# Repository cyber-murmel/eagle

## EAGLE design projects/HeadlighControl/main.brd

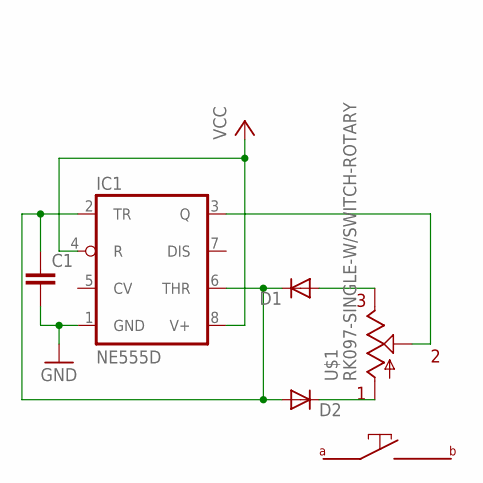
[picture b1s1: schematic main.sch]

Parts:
C1: C-EUC0603; C0603
D1, D2: DIODE-MICROMELF-W; MICROMELF-W
IC1: NE555D; SO08
U$1: RK097-SINGLE-W/SWITCH-ROTARY; RK097-DUAL-ELEMENT-W/SWITCH

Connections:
GND: C1.2, IC1.1 (GND)
unnamed: IC1.3 (Q), U$1.P$5 (S), U$1.P$6 (S1)
unnamed: D2.C, U$1.P$1 (A), U$1.P$2 (A1)
unnamed: D1.A, U$1.P$3 (E), U$1.P$4 (E1)
unnamed: C1.1, D1.C, D2.A, IC1.2 (TR), IC1.6 (THR)
VCC: IC1.4 (R), IC1.8 (V+)

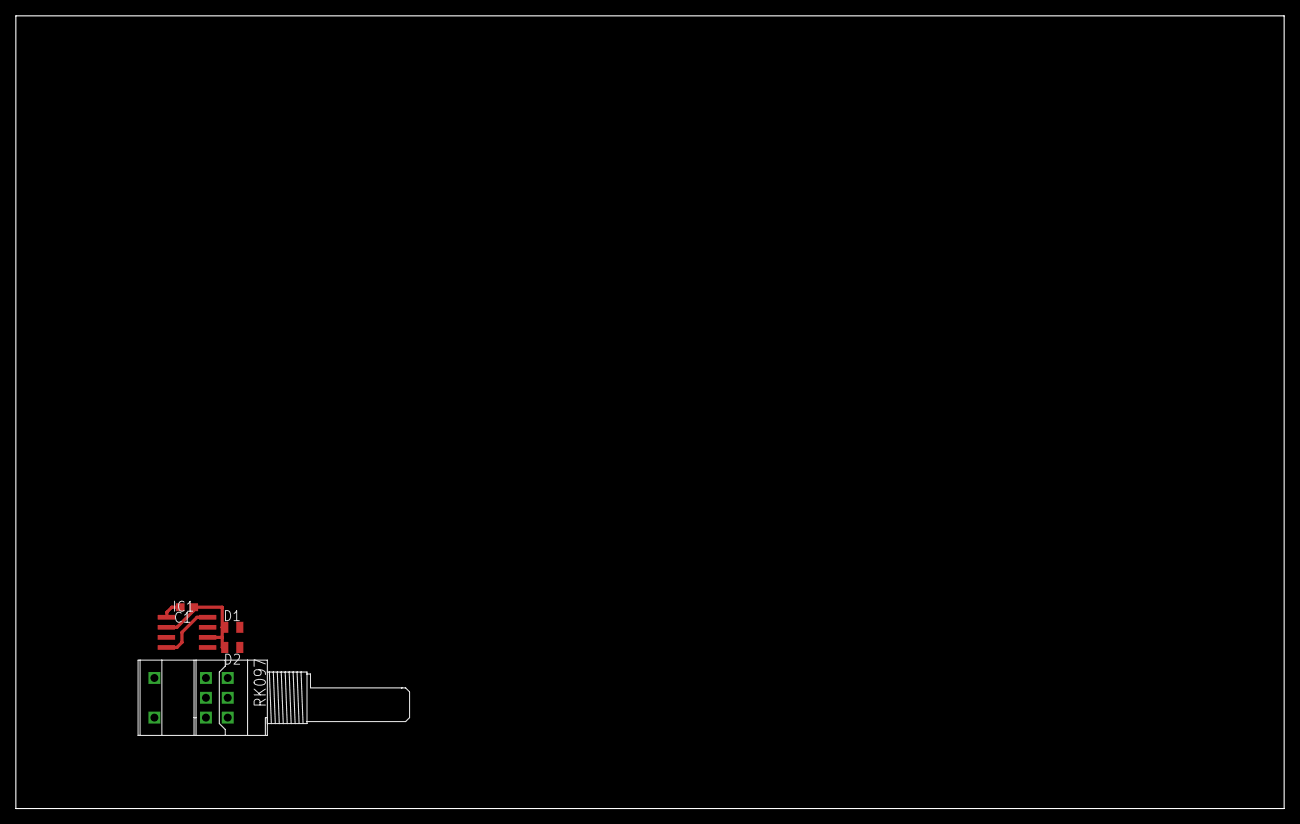
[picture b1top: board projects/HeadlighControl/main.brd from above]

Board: 2 copper layers, 160.0 x 100.0 mm, 5 parts (0 on the bottom side), 6 nets.

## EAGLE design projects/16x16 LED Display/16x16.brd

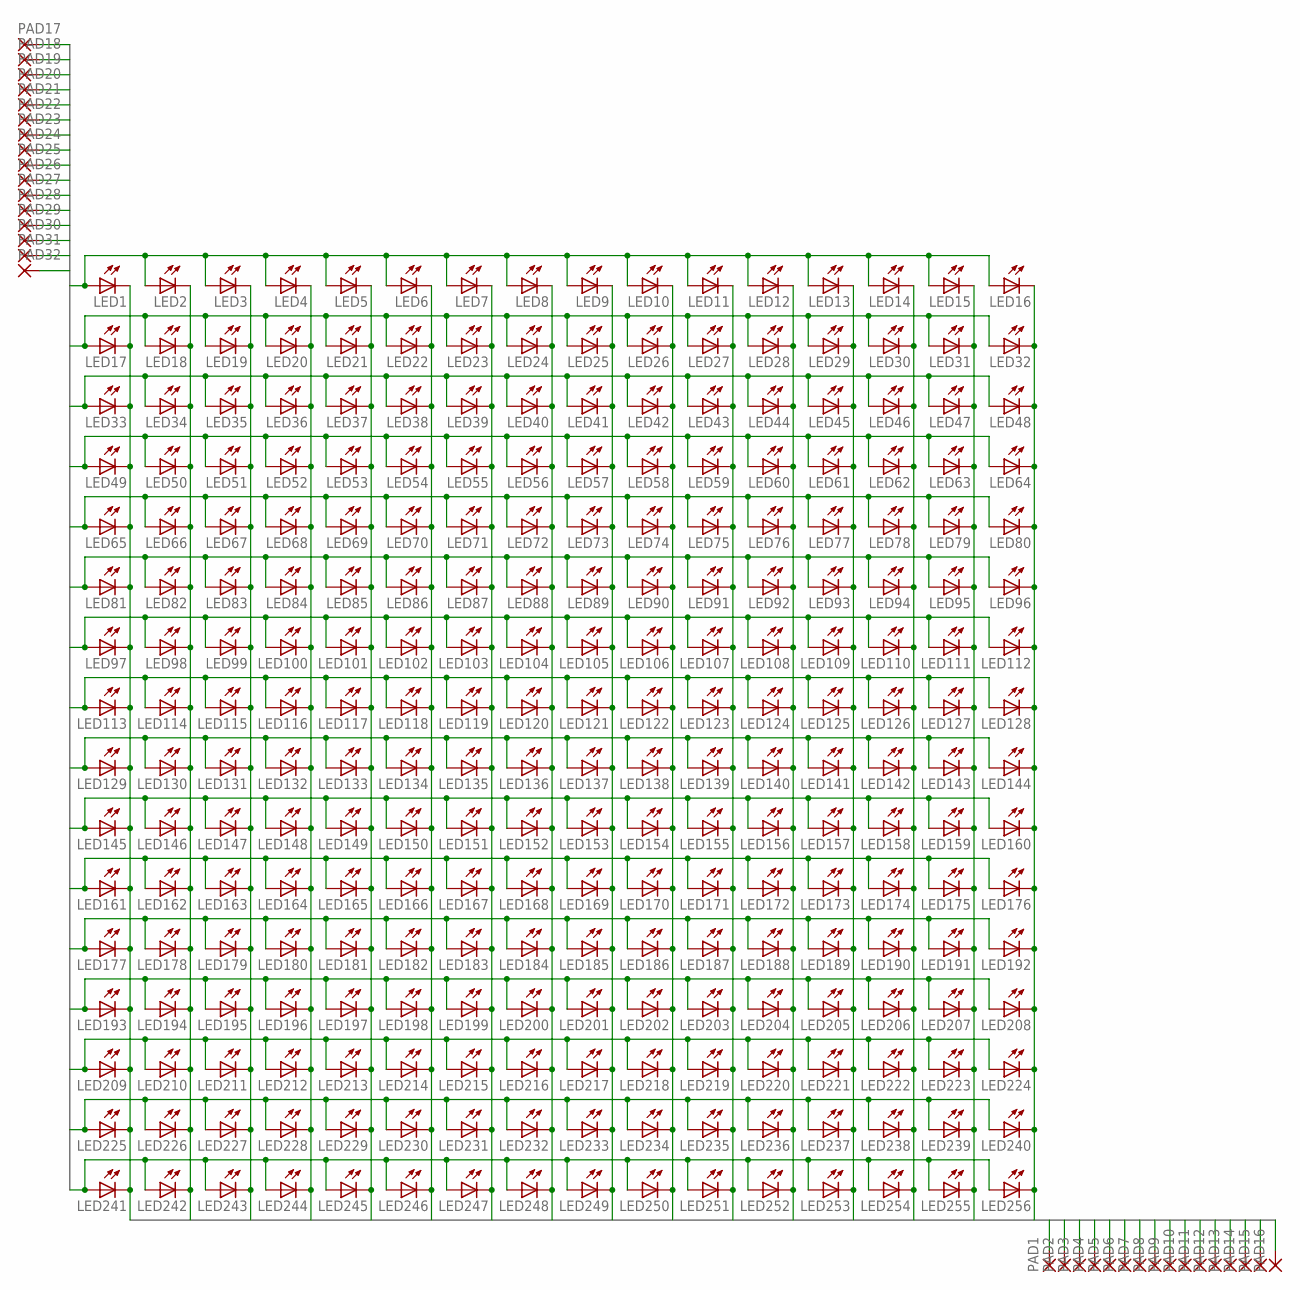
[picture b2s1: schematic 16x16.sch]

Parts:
LED1, LED2, LED3, LED4, LED5, LED6, LED7, LED8, LED9, LED10, LED11, LED12, LED13, LED14, LED15, LED16, LED17, LED18, LED19, LED20, LED21, LED22, LED23, LED24, LED25, LED26, LED27, LED28, LED29, LED30, LED31, LED32, LED33, LED34, LED35, LED36, LED37, LED38, LED39, LED40, LED41, LED42, LED43, LED44, LED45, LED46, LED47, LED48, LED49, LED50, LED51, LED52, LED53, LED54, LED55, LED56, LED57, LED58, LED59, LED60, LED61, LED62, LED63, LED64, LED65, LED66, LED67, LED68, LED69, LED70, LED71, LED72, LED73, LED74, LED75, LED76, LED77, LED78, LED79, LED80, LED81, LED82, LED83, LED84, LED85, LED86, LED87, LED88, LED89, LED90, LED91, LED92, LED93, LED94, LED95, LED96, LED97, LED98, LED99, LED100, LED101, LED102, LED103, LED104, LED105, LED106, LED107, LED108, LED109, LED110, LED111, LED112, LED113, LED114, LED115, LED116, LED117, LED118, LED119, LED120, LED121, LED122, LED123, LED124, LED125, LED126, LED127, LED128, LED129, LED130, LED131, LED132, LED133, LED134, LED135, LED136, LED137, LED138, LED139, LED140, LED141, LED142, LED143, LED144, LED145, LED146, LED147, LED148, LED149, LED150, LED151, LED152, LED153, LED154, LED155, LED156, LED157, LED158, LED159, LED160, LED161, LED162, LED163, LED164, LED165, LED166, LED167, LED168, LED169, LED170, LED171, LED172, LED173, LED174, LED175, LED176, LED177, LED178, LED179, LED180, LED181, LED182, LED183, LED184, LED185, LED186, LED187, LED188, LED189, LED190, LED191, LED192, LED193, LED194, LED195, LED196, LED197, LED198, LED199, LED200, LED201, LED202, LED203, LED204, LED205, LED206, LED207, LED208, LED209, LED210, LED211, LED212, LED213, LED214, LED215, LED216, LED217, LED218, LED219, LED220, LED221, LED222, LED223, LED224, LED225, LED226, LED227, LED228, LED229, LED230, LED231, LED232, LED233, LED234, LED235, LED236, LED237, LED238, LED239, LED240, LED241, LED242, LED243, LED244, LED245, LED246, LED247, LED248, LED249, LED250, LED251, LED252, LED253, LED254, LED255, LED256: LEDSML0603; SML0603
PAD1, PAD2, PAD3, PAD4, PAD5, PAD6, PAD7, PAD8, PAD9, PAD10, PAD11, PAD12, PAD13, PAD14, PAD15, PAD16, PAD17, PAD18, PAD19, PAD20, PAD21, PAD22, PAD23, PAD24, PAD25, PAD26, PAD27, PAD28, PAD29, PAD30, PAD31, PAD32: SMD2; SMD1,27-2,54

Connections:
X0: LED1.C, LED17.C, LED33.C, LED49.C, LED65.C, LED81.C, LED97.C, LED113.C, LED129.C, LED145.C, LED161.C, LED177.C, LED193.C, LED209.C, LED225.C, LED241.C, PAD1.1
X1: LED2.C, LED18.C, LED34.C, LED50.C, LED66.C, LED82.C, LED98.C, LED114.C, LED130.C, LED146.C, LED162.C, LED178.C, LED194.C, LED210.C, LED226.C, LED242.C, PAD2.1
X2: LED3.C, LED19.C, LED35.C, LED51.C, LED67.C, LED83.C, LED99.C, LED115.C, LED131.C, LED147.C, LED163.C, LED179.C, LED195.C, LED211.C, LED227.C, LED243.C, PAD3.1
X3: LED4.C, LED20.C, LED36.C, LED52.C, LED68.C, LED84.C, LED100.C, LED116.C, LED132.C, LED148.C, LED164.C, LED180.C, LED196.C, LED212.C, LED228.C, LED244.C, PAD4.1
X4: LED5.C, LED21.C, LED37.C, LED53.C, LED69.C, LED85.C, LED101.C, LED117.C, LED133.C, LED149.C, LED165.C, LED181.C, LED197.C, LED213.C, LED229.C, LED245.C, PAD5.1
X5: LED6.C, LED22.C, LED38.C, LED54.C, LED70.C, LED86.C, LED102.C, LED118.C, LED134.C, LED150.C, LED166.C, LED182.C, LED198.C, LED214.C, LED230.C, LED246.C, PAD6.1
X6: LED7.C, LED23.C, LED39.C, LED55.C, LED71.C, LED87.C, LED103.C, LED119.C, LED135.C, LED151.C, LED167.C, LED183.C, LED199.C, LED215.C, LED231.C, LED247.C, PAD7.1
X7: LED8.C, LED24.C, LED40.C, LED56.C, LED72.C, LED88.C, LED104.C, LED120.C, LED136.C, LED152.C, LED168.C, LED184.C, LED200.C, LED216.C, LED232.C, LED248.C, PAD8.1
X8: LED9.C, LED25.C, LED41.C, LED57.C, LED73.C, LED89.C, LED105.C, LED121.C, LED137.C, LED153.C, LED169.C, LED185.C, LED201.C, LED217.C, LED233.C, LED249.C, PAD9.1
X9: LED10.C, LED26.C, LED42.C, LED58.C, LED74.C, LED90.C, LED106.C, LED122.C, LED138.C, LED154.C, LED170.C, LED186.C, LED202.C, LED218.C, LED234.C, LED250.C, PAD10.1
X10: LED11.C, LED27.C, LED43.C, LED59.C, LED75.C, LED91.C, LED107.C, LED123.C, LED139.C, LED155.C, LED171.C, LED187.C, LED203.C, LED219.C, LED235.C, LED251.C, PAD11.1
X11: LED12.C, LED28.C, LED44.C, LED60.C, LED76.C, LED92.C, LED108.C, LED124.C, LED140.C, LED156.C, LED172.C, LED188.C, LED204.C, LED220.C, LED236.C, LED252.C, PAD12.1
X12: LED13.C, LED29.C, LED45.C, LED61.C, LED77.C, LED93.C, LED109.C, LED125.C, LED141.C, LED157.C, LED173.C, LED189.C, LED205.C, LED221.C, LED237.C, LED253.C, PAD13.1
X13: LED14.C, LED30.C, LED46.C, LED62.C, LED78.C, LED94.C, LED110.C, LED126.C, LED142.C, LED158.C, LED174.C, LED190.C, LED206.C, LED222.C, LED238.C, LED254.C, PAD14.1
X14: LED15.C, LED31.C, LED47.C, LED63.C, LED79.C, LED95.C, LED111.C, LED127.C, LED143.C, LED159.C, LED175.C, LED191.C, LED207.C, LED223.C, LED239.C, LED255.C, PAD15.1
X15: LED16.C, LED32.C, LED48.C, LED64.C, LED80.C, LED96.C, LED112.C, LED128.C, LED144.C, LED160.C, LED176.C, LED192.C, LED208.C, LED224.C, LED240.C, LED256.C, PAD16.1
Y0: LED1.A, LED2.A, LED3.A, LED4.A, LED5.A, LED6.A, LED7.A, LED8.A, LED9.A, LED10.A, LED11.A, LED12.A, LED13.A, LED14.A, LED15.A, LED16.A, PAD17.1
Y1: LED17.A, LED18.A, LED19.A, LED20.A, LED21.A, LED22.A, LED23.A, LED24.A, LED25.A, LED26.A, LED27.A, LED28.A, LED29.A, LED30.A, LED31.A, LED32.A, PAD18.1
Y2: LED33.A, LED34.A, LED35.A, LED36.A, LED37.A, LED38.A, LED39.A, LED40.A, LED41.A, LED42.A, LED43.A, LED44.A, LED45.A, LED46.A, LED47.A, LED48.A, PAD19.1
Y3: LED49.A, LED50.A, LED51.A, LED52.A, LED53.A, LED54.A, LED55.A, LED56.A, LED57.A, LED58.A, LED59.A, LED60.A, LED61.A, LED62.A, LED63.A, LED64.A, PAD20.1
Y4: LED65.A, LED66.A, LED67.A, LED68.A, LED69.A, LED70.A, LED71.A, LED72.A, LED73.A, LED74.A, LED75.A, LED76.A, LED77.A, LED78.A, LED79.A, LED80.A, PAD21.1
Y5: LED81.A, LED82.A, LED83.A, LED84.A, LED85.A, LED86.A, LED87.A, LED88.A, LED89.A, LED90.A, LED91.A, LED92.A, LED93.A, LED94.A, LED95.A, LED96.A, PAD22.1
Y6: LED97.A, LED98.A, LED99.A, LED100.A, LED101.A, LED102.A, LED103.A, LED104.A, LED105.A, LED106.A, LED107.A, LED108.A, LED109.A, LED110.A, LED111.A, LED112.A, PAD23.1
Y7: LED113.A, LED114.A, LED115.A, LED116.A, LED117.A, LED118.A, LED119.A, LED120.A, LED121.A, LED122.A, LED123.A, LED124.A, LED125.A, LED126.A, LED127.A, LED128.A, PAD24.1
Y8: LED129.A, LED130.A, LED131.A, LED132.A, LED133.A, LED134.A, LED135.A, LED136.A, LED137.A, LED138.A, LED139.A, LED140.A, LED141.A, LED142.A, LED143.A, LED144.A, PAD25.1
Y9: LED145.A, LED146.A, LED147.A, LED148.A, LED149.A, LED150.A, LED151.A, LED152.A, LED153.A, LED154.A, LED155.A, LED156.A, LED157.A, LED158.A, LED159.A, LED160.A, PAD26.1
Y10: LED161.A, LED162.A, LED163.A, LED164.A, LED165.A, LED166.A, LED167.A, LED168.A, LED169.A, LED170.A, LED171.A, LED172.A, LED173.A, LED174.A, LED175.A, LED176.A, PAD27.1
Y11: LED177.A, LED178.A, LED179.A, LED180.A, LED181.A, LED182.A, LED183.A, LED184.A, LED185.A, LED186.A, LED187.A, LED188.A, LED189.A, LED190.A, LED191.A, LED192.A, PAD28.1
Y12: LED193.A, LED194.A, LED195.A, LED196.A, LED197.A, LED198.A, LED199.A, LED200.A, LED201.A, LED202.A, LED203.A, LED204.A, LED205.A, LED206.A, LED207.A, LED208.A, PAD29.1
Y13: LED209.A, LED210.A, LED211.A, LED212.A, LED213.A, LED214.A, LED215.A, LED216.A, LED217.A, LED218.A, LED219.A, LED220.A, LED221.A, LED222.A, LED223.A, LED224.A, PAD30.1
Y14: LED225.A, LED226.A, LED227.A, LED228.A, LED229.A, LED230.A, LED231.A, LED232.A, LED233.A, LED234.A, LED235.A, LED236.A, LED237.A, LED238.A, LED239.A, LED240.A, PAD31.1
Y15: LED241.A, LED242.A, LED243.A, LED244.A, LED245.A, LED246.A, LED247.A, LED248.A, LED249.A, LED250.A, LED251.A, LED252.A, LED253.A, LED254.A, LED255.A, LED256.A, PAD32.1

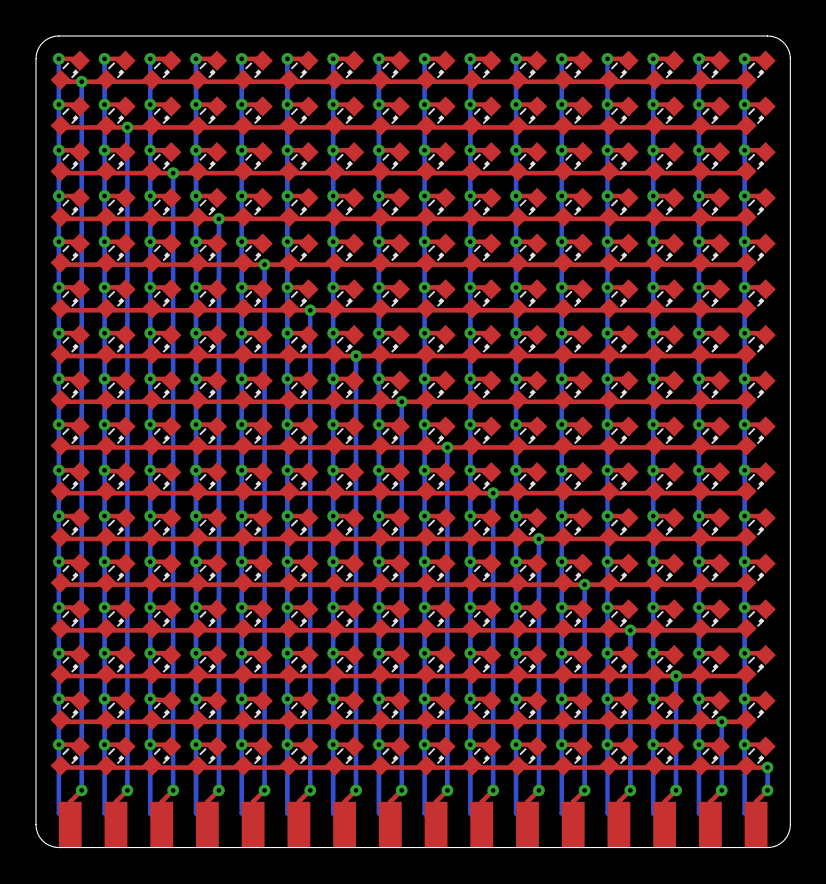
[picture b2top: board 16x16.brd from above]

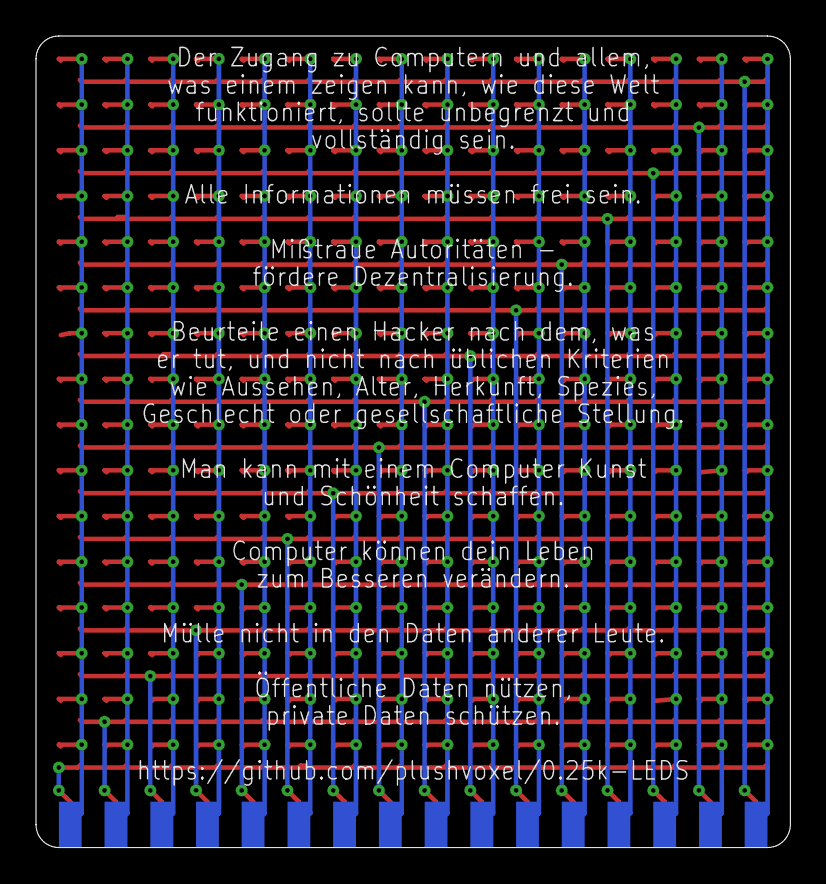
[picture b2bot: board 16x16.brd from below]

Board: 2 copper layers, 41.9 x 45.1 mm, 288 parts (16 on the bottom side), 32 nets.

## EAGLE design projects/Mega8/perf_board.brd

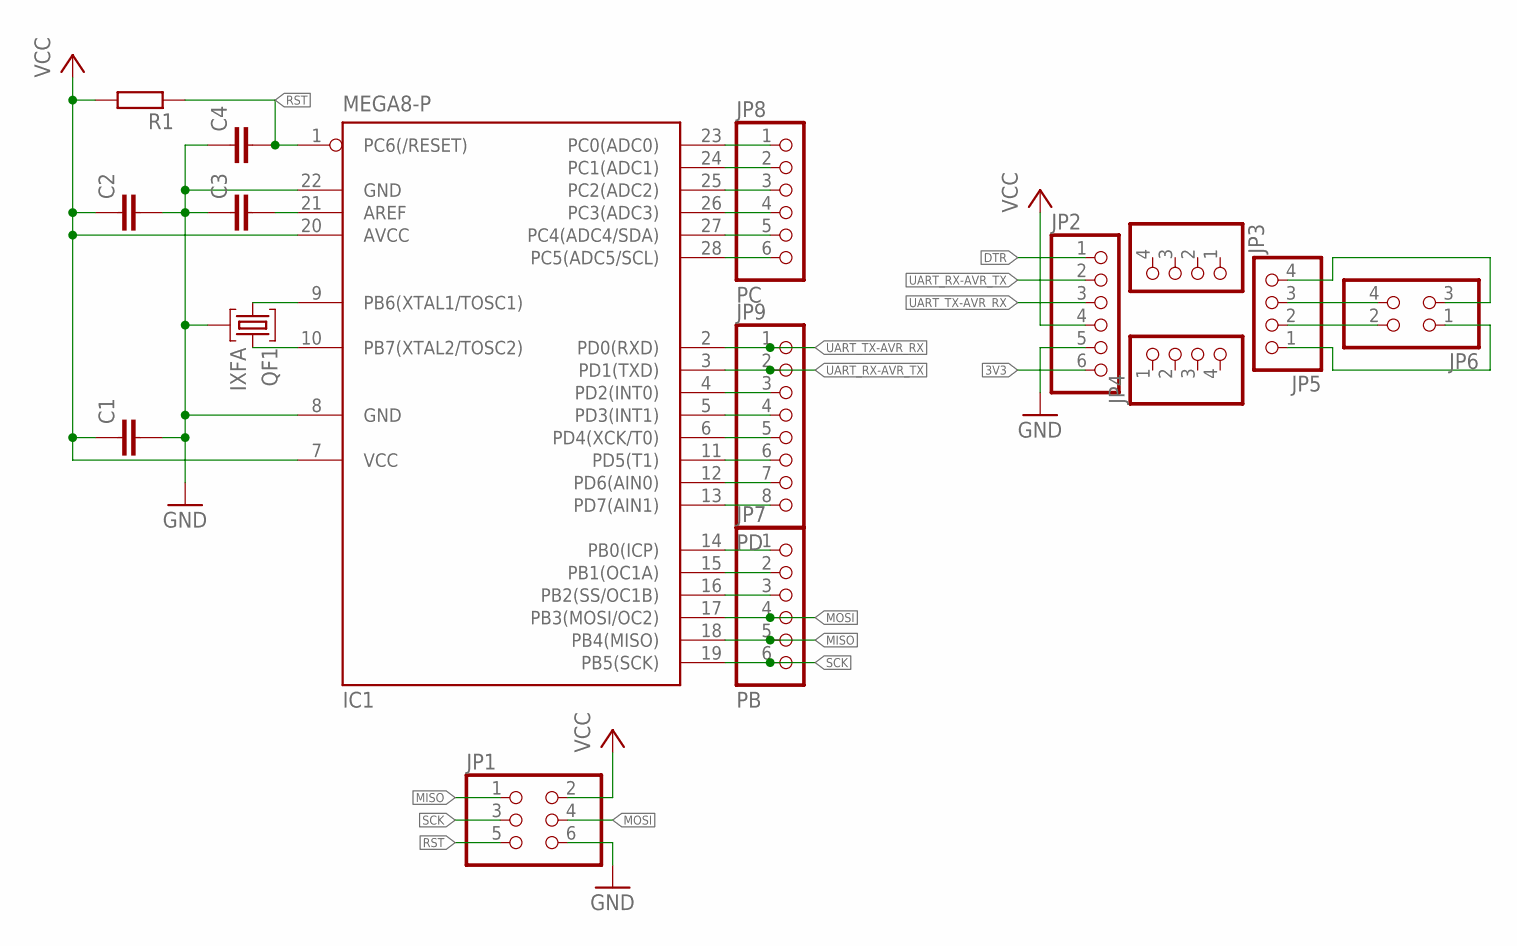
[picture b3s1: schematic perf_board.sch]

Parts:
C1, C2, C3, C4: C-EUC0603; C0603
IC1: MEGA8-P; DIL28-3
JP1: PINHD-2X3; 2X03
JP2: PINHD-1X6; 1X06
JP3, JP4, JP5: PINHD-1X4; 1X04
JP6: PINHD-2X2; 2X02
JP7: PB; 1X06
JP8: PC; 1X06
JP9: PD; 1X08
QF1: IXFA; HC49U
R1: R-EU_R0603; R0603

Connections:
3V3: JP2.6
DTR: JP2.1
GND: C1.2, C2.2, C3.1, C4.1, IC1.8 (GND), IC1.22 (GND), JP1.6, JP2.5, QF1.2
MISO: IC1.18 (PB4(MISO)), JP1.1, JP7.5
MOSI: IC1.17 (PB3(MOSI/OC2)), JP1.4, JP7.4
unnamed: C3.2, IC1.21 (AREF)
unnamed: IC1.9 (PB6(XTAL1/TOSC1)), QF1.1
unnamed: IC1.10 (PB7(XTAL2/TOSC2)), QF1.3
unnamed: JP5.2, JP6.2
unnamed: JP5.1, JP6.1
unnamed: JP5.3, JP6.4
unnamed: JP5.4, JP6.3
unnamed: IC1.14 (PB0(ICP)), JP7.1
unnamed: IC1.15 (PB1(OC1A)), JP7.2
unnamed: IC1.16 (PB2(SS/OC1B)), JP7.3
unnamed: IC1.4 (PD2(INT0)), JP9.3
unnamed: IC1.5 (PD3(INT1)), JP9.4
unnamed: IC1.6 (PD4(XCK/T0)), JP9.5
unnamed: IC1.11 (PD5(T1)), JP9.6
unnamed: IC1.12 (PD6(AIN0)), JP9.7
unnamed: IC1.13 (PD7(AIN1)), JP9.8
unnamed: IC1.23 (PC0(ADC0)), JP8.1
unnamed: IC1.24 (PC1(ADC1)), JP8.2
unnamed: IC1.25 (PC2(ADC2)), JP8.3
unnamed: IC1.26 (PC3(ADC3)), JP8.4
unnamed: IC1.27 (PC4(ADC4/SDA)), JP8.5
unnamed: IC1.28 (PC5(ADC5/SCL)), JP8.6
RST: C4.2, IC1.1 (PC6(/RESET)), JP1.5, R1.1
SCK: IC1.19 (PB5(SCK)), JP1.3, JP7.6
UART_RX-AVR_TX: IC1.3 (PD1(TXD)), JP2.2, JP9.2
UART_TX-AVR_RX: IC1.2 (PD0(RXD)), JP2.3, JP9.1
VCC: C1.1, C2.1, IC1.7 (VCC), IC1.20 (AVCC), JP1.2, JP2.4, R1.2

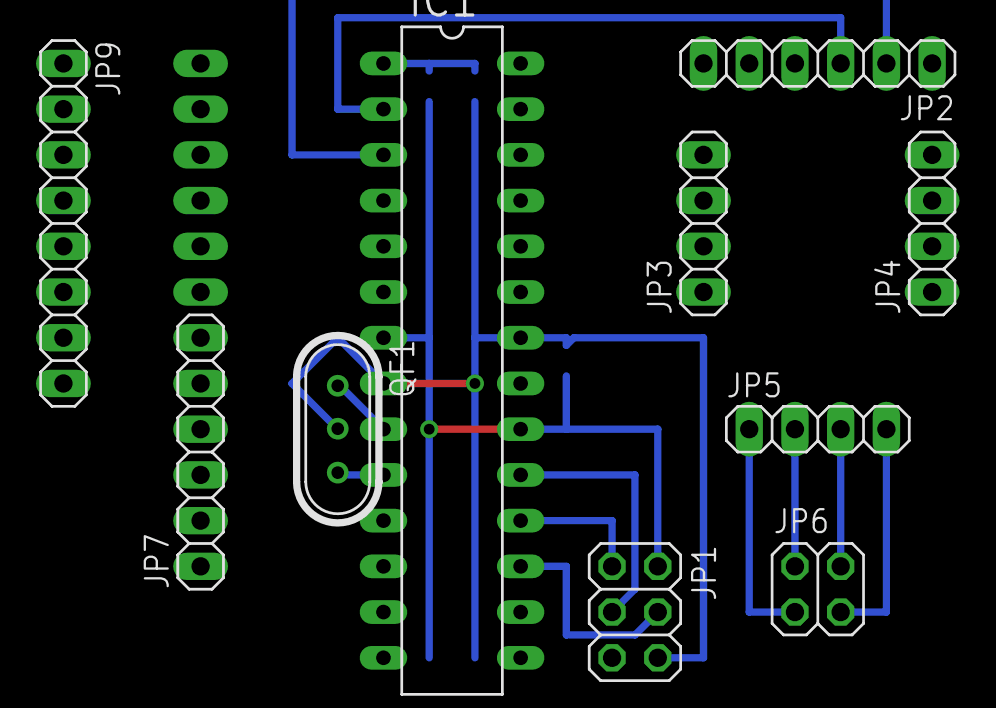
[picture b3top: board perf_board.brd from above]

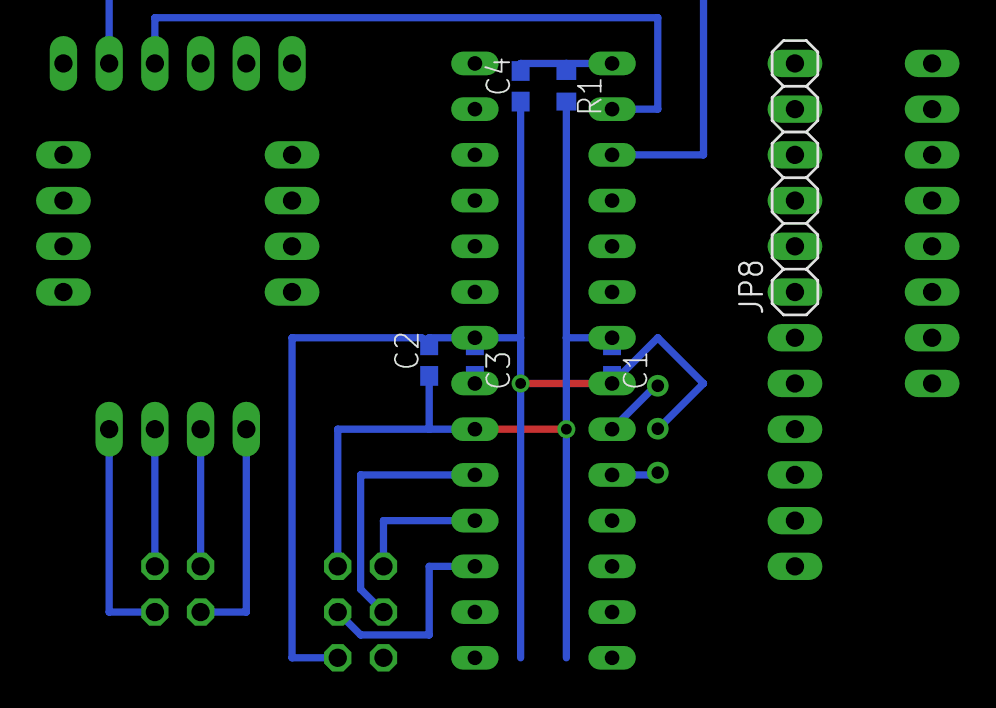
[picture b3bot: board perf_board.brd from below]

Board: 2 copper layers, 16 parts (6 on the bottom side), 30 nets.

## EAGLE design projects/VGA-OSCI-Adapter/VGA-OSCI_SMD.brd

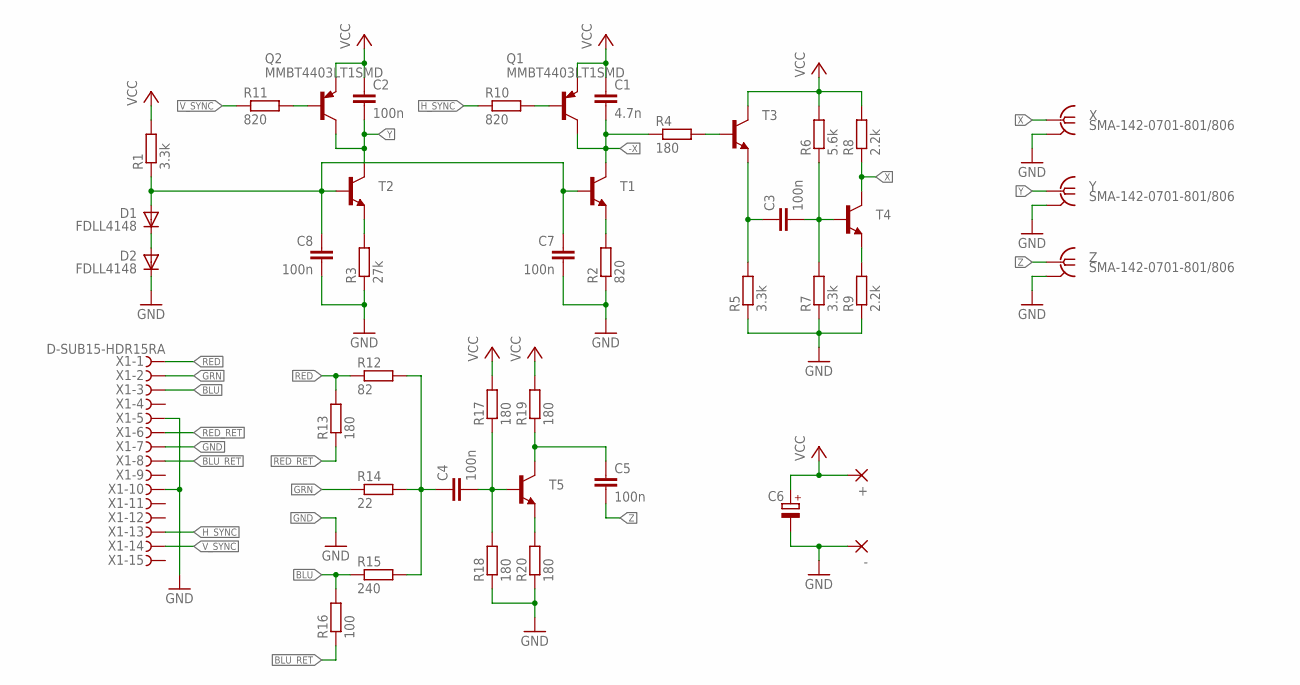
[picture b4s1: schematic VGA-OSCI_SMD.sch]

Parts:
+: WIREPADSMD1,27-254; SMD1,27-2,54
-: WIREPADSMD1,27-254; SMD1,27-2,54
C1: 4.7n; C0603
C2, C3, C4, C5, C7, C8: 100n; C0603
C6: CPOL-EU153CLV-0810; 153CLV-0810
D1, D2: FDLL4148; SOD80C
Q1, Q2: MMBT4403LT1SMD; SOT23-BEC
R1, R5, R7: 3.3k; R0603
R2, R10, R11: 820; R0603
R3: 27k; R0603
R4, R13, R17, R18, R19, R20: 180; R0603
R6: 5.6k; R0603
R8, R9: 2.2k; R0603
R12: 82; R0603
R14: 22; R0603
R15: 240; R0603
R16: 100; R0603
T1, T2, T3, T4, T5: MMBT2222ALT1-NPN-SOT23-BEC; SOT23-BEC
X: SMA-142-0701-801/806; J502-ND-142-0701-801/806
X1: D-SUB15-HDR15RA; HDR15RA
Y: SMA-142-0701-801/806; J502-ND-142-0701-801/806
Z: SMA-142-0701-801/806; J502-ND-142-0701-801/806

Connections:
-X: C1.2, Q1.C, R4.1, T1.C
BLU: R15.1, R16.2, X1.3
BLU_RET: R16.1, X1.8
GND: -.1, C6.-, C7.2, C8.2, D2.C, R2.1, R3.1, R5.1, R7.1, R9.1, R18.1, R20.1, X.G@1 (2), X.G@2 (2), X.G@3 (2), X.G@4 (2), X1.5, X1.7, X1.10, Y.G@1 (2), Y.G@2 (2), Y.G@3 (2), Y.G@4 (2), Z.G@1 (2), Z.G@2 (2), Z.G@3 (2), Z.G@4 (2)
GRN: R14.1, X1.2
GRY_SCL: C4.1, R12.2, R14.2, R15.2
H_SYNC: R10.1, X1.13
unnamed: D1.C, D2.A
unnamed: C7.1, C8.1, D1.A, R1.1, T1.B, T2.B
unnamed: R2.2, T1.E
unnamed: R3.2, T2.E
unnamed: Q2.B, R11.2
unnamed: R9.2, T4.E
unnamed: C3.2, R6.1, R7.2, T4.B
unnamed: C3.1, R5.2, T3.E
unnamed: R4.2, T3.B
unnamed: Q1.B, R10.2
unnamed: C4.2, R17.1, R18.2, T5.B
unnamed: C5.1, R19.1, T5.C
unnamed: R20.2, T5.E
RED: R12.1, R13.2, X1.1
RED_RET: R13.1, X1.6
VCC: +.1, C1.1, C2.1, C6.+, Q1.E, Q2.E, R1.2, R6.2, R8.2, R17.2, R19.2, T3.C
V_SYNC: R11.1, X1.14
X: R8.1, T4.C, X.1
Y: C2.2, Q2.C, T2.C, Y.1
Z: C5.2, Z.1

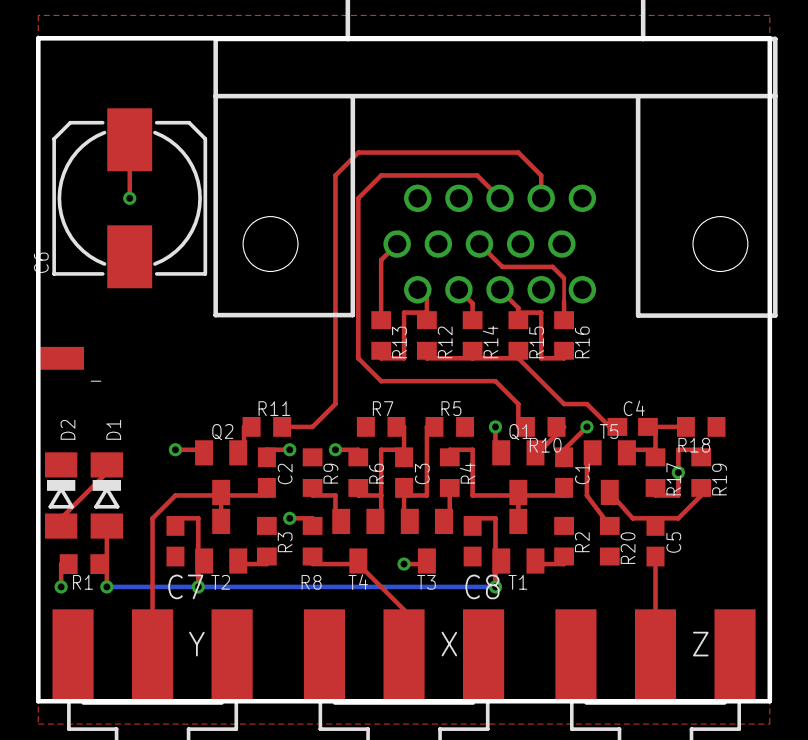
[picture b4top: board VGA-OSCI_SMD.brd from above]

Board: 2 copper layers, 40.6 x 36.8 mm, 43 parts (1 on the bottom side), 27 nets.

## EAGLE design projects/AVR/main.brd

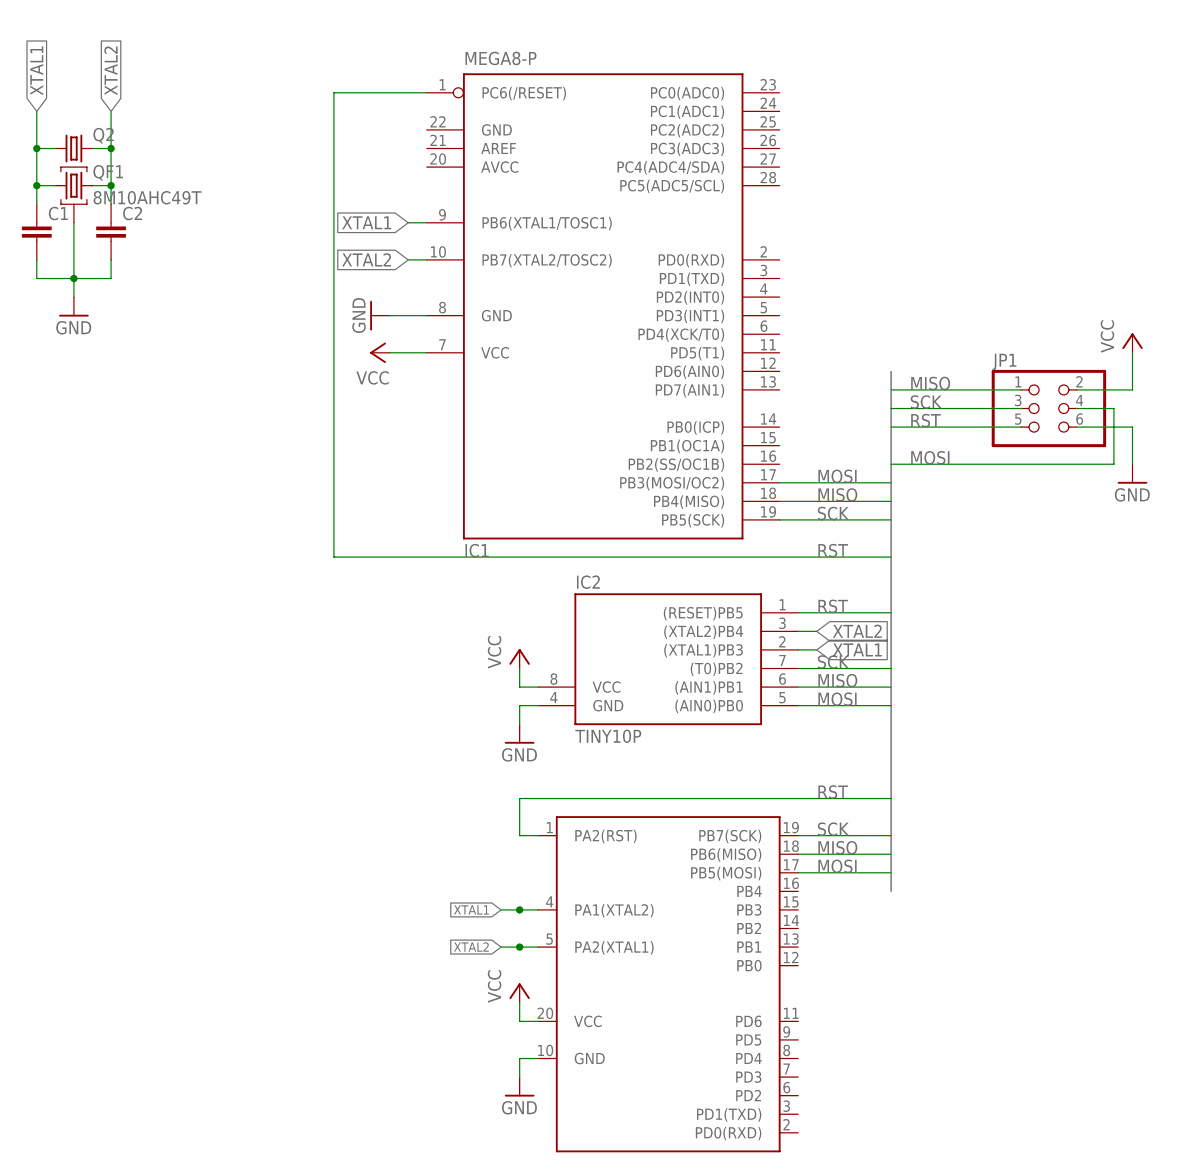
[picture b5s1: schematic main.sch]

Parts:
C1, C2: C-EUC0603K; C0603K
IC1: MEGA8-P; DIL28-3
IC2: TINY10P; DIL08
JP1: PINHD-2X3; 2X03
Q2: CRYSTALHC18U-V; HC18U-V
QF1: 8M10AHC49T; HC49U
U$1: TINY2313; DIL20

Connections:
AVCC: IC1.20 (AVCC)
GND: C1.2, C2.2, IC1.8 (GND), IC1.22 (GND), IC2.4 (GND), JP1.6, QF1.2, U$1.10 (GND)
MISO: IC1.18 (PB4(MISO)), IC2.6 ((AIN1)PB1), JP1.1, U$1.18 (PB6(MISO))
MOSI: IC1.17 (PB3(MOSI/OC2)), IC2.5 ((AIN0)PB0), JP1.4, U$1.17 (PB5(MOSI))
RST: IC1.1 (PC6(/RESET)), IC2.1 ((RESET)PB5), JP1.5, U$1.1 (PA2(RST))
SCK: IC1.19 (PB5(SCK)), IC2.7 ((T0)PB2), JP1.3, U$1.19 (PB7(SCK))
VCC: IC1.7 (VCC), IC2.8 (VCC), JP1.2, U$1.20 (VCC)
XTAL1: C1.1, IC1.9 (PB6(XTAL1/TOSC1)), IC2.2 ((XTAL1)PB3), Q2.1, QF1.1, U$1.4 (PA1(XTAL2))
XTAL2: C2.1, IC1.10 (PB7(XTAL2/TOSC2)), IC2.3 ((XTAL2)PB4), Q2.2, QF1.3, U$1.5 (PA2(XTAL1))

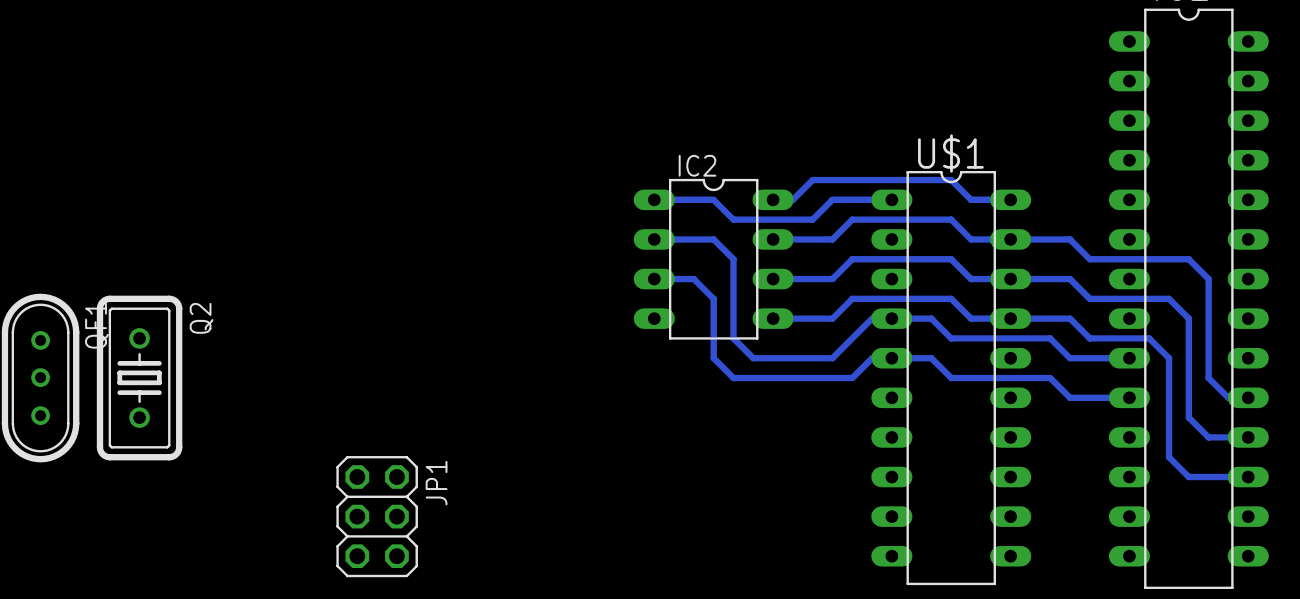
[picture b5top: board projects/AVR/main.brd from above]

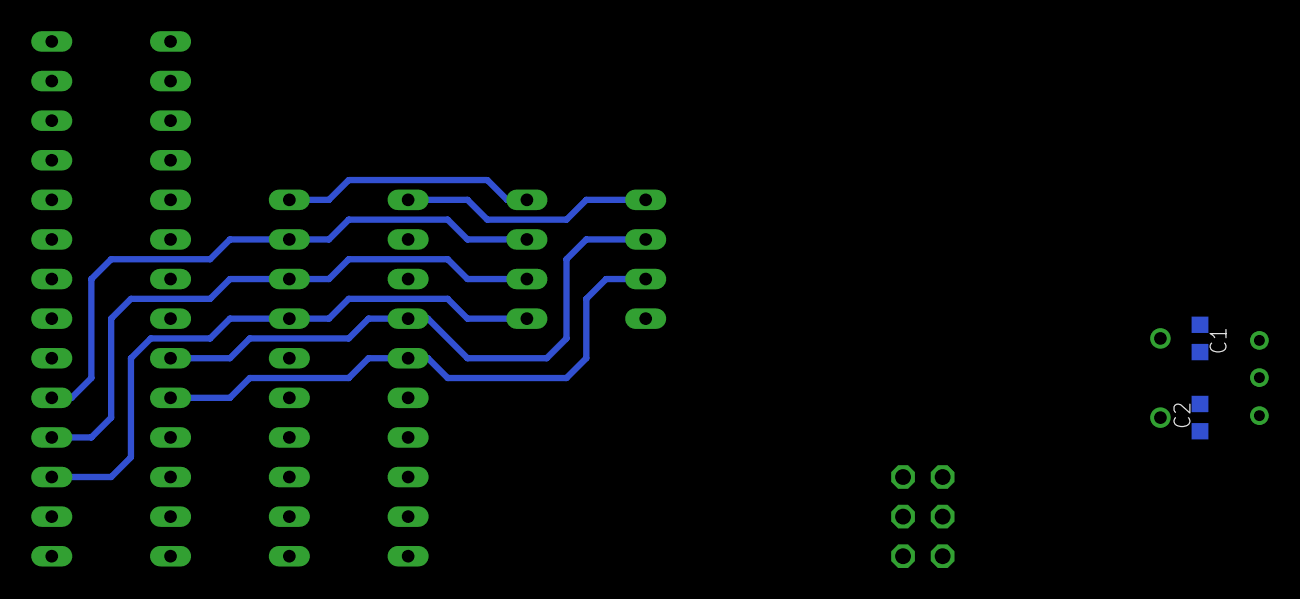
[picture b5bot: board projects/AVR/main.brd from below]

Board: 2 copper layers, 8 parts (2 on the bottom side), 8 nets.

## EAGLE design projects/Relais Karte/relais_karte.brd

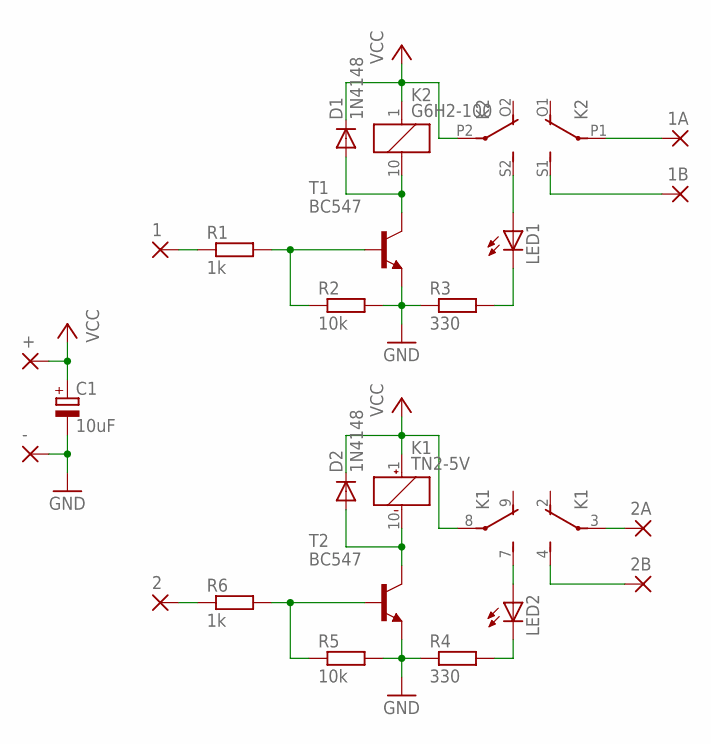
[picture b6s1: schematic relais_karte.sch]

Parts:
1, 1A, 1B, 2, 2A, 2B: WIREPAD2,15/1,0; 2,15/1,0
+: WIREPAD2,15/1,0; 2,15/1,0
-: WIREPAD2,15/1,0; 2,15/1,0
C1: 10uF; B45181A
D1, D2: 1N4148; DO35-7
K1: TN2-5V; TN2
K2: G6H2-100
LED1, LED2: LED5MM
R1, R6: 1k; 0204/7
R2, R5: 10k; 0204/7
R3, R4: 330; 0204/7
T1, T2: BC547; TO92-EBC

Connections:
GND: -.1, C1.-, R2.2, R3.1, R4.1, R5.2, T1.E, T2.E
unnamed: D1.A, K2.10 (2), T1.C
unnamed: LED1.K (C), R3.2
unnamed: K2.S2 (S), LED1.A
unnamed: 1B.1, K2.S1 (S)
unnamed: R1.2, R2.1, T1.B
unnamed: 1A.1, K2.P1
unnamed: 1.1, R1.1
unnamed: D2.A, K1.10 (-), T2.C
unnamed: LED2.K (C), R4.2
unnamed: K1.7 (S), LED2.A
unnamed: R5.1, R6.2, T2.B
unnamed: 2.1, R6.1
unnamed: 2B.1, K1.4 (S)
unnamed: 2A.1, K1.3
VCC: +.1, C1.+, D1.C, D2.C, K1.1 (+), K1.8, K2.1, K2.P2

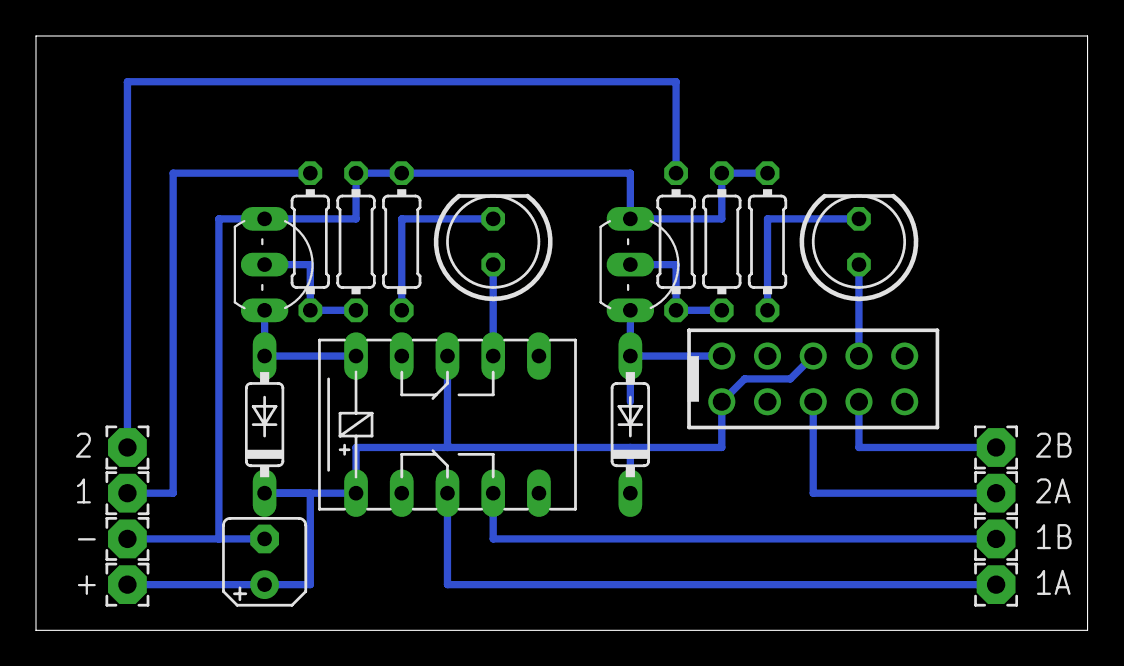
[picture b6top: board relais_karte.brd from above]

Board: 2 copper layers, 58.4 x 33.0 mm, 23 parts (0 on the bottom side), 16 nets.

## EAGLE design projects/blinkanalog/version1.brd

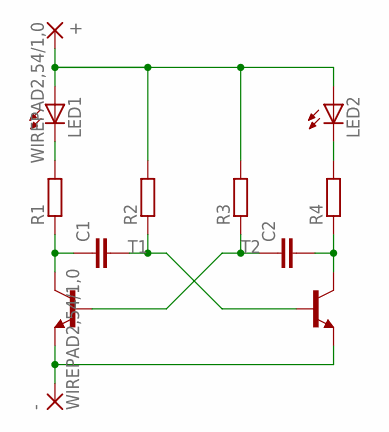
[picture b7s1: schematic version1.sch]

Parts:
+: WIREPAD2,54/1,0; 2,54/1,0
-: WIREPAD2,54/1,0; 2,54/1,0
C1, C2: C-EUC0603; C0603
LED1, LED2: LEDSML0603; SML0603
R1, R2, R3, R4: R-EU_R0603; R0603
T1, T2: MMBT2222ALT1-NPN-SOT23-BEC; SOT23-BEC

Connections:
unnamed: LED1.C, R1.2
unnamed: C1.1, R1.1, T1.C
unnamed: C2.2, R4.1, T2.C
unnamed: LED2.C, R4.2
unnamed: C1.2, R2.1, T2.B
unnamed: C2.1, R3.1, T1.B
unnamed: +.1, LED1.A, LED2.A, R2.2, R3.2
unnamed: -.1, T1.E, T2.E

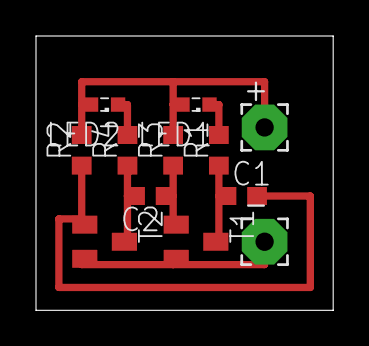
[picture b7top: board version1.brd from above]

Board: 2 copper layers, 16.5 x 15.2 mm, 12 parts (0 on the bottom side), 8 nets.

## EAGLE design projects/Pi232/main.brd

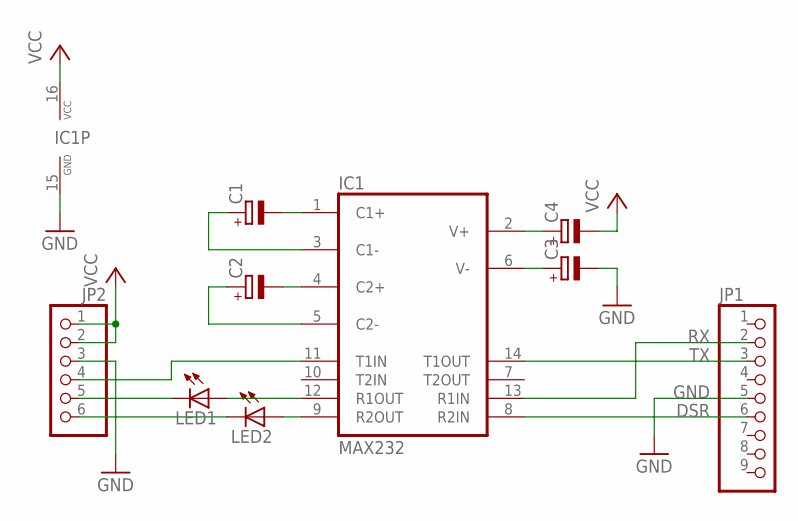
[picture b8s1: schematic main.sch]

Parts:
C1, C2, C3, C4: CPOL-EUB45181A; B45181A
IC1: MAX232; DIL16
JP1: PINHD-1X9; 1X09
JP2: PINHD-1X6; 1X06
LED1, LED2: LED3MM

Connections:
DSR: IC1.8 (R2IN), JP1.6
GND: C3.-, IC1.15 (GND), JP1.5, JP2.3
GPIO18: JP2.6, LED2.K (C)
unnamed: C3.+, IC1.6 (V-)
unnamed: C4.+, IC1.2 (V+)
unnamed: C1.+, IC1.3 (C1-)
unnamed: C1.-, IC1.1 (C1+)
unnamed: C2.+, IC1.5 (C2-)
unnamed: C2.-, IC1.4 (C2+)
unnamed: IC1.12 (R1OUT), LED1.A
unnamed: IC1.9 (R2OUT), LED2.A
RX: IC1.13 (R1IN), JP1.2
RXD: JP2.5, LED1.K (C)
TX: IC1.14 (T1OUT), JP1.3
TXD: IC1.11 (T1IN), JP2.4
VCC: C4.-, IC1.16 (VCC), JP2.1, JP2.2
